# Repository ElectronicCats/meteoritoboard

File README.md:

# Meteorito Board

Kit de estación meteorologica para "Curso de estación y fenómenos meteorológicos" que funciona con La Red Meteorológica Ambiental([RedMet](http://redmet.org/)) promueve la difusión y concientización del cambio climático global. 

Manual, guía de arranque, curso completo y más información en [Pagina Oficial](http://meteorito.mx/index.html)

Electronic Cats invests time and resources providing this open source design, please support Electronic Cats and open-source hardware by purchasing products from Electronic Cats!

Designed by Electronic Cats.

Firmware released under an GNU AGPL v3.0 license. See the LICENSE file for more information.

Hardware released under an CERN Open Hardware Licence v1.2. See the LICENSE_HARDWARE file for more information.

Electronic Cats is a registered trademark, please do not use if you sell these PCBs.

22 July 2017

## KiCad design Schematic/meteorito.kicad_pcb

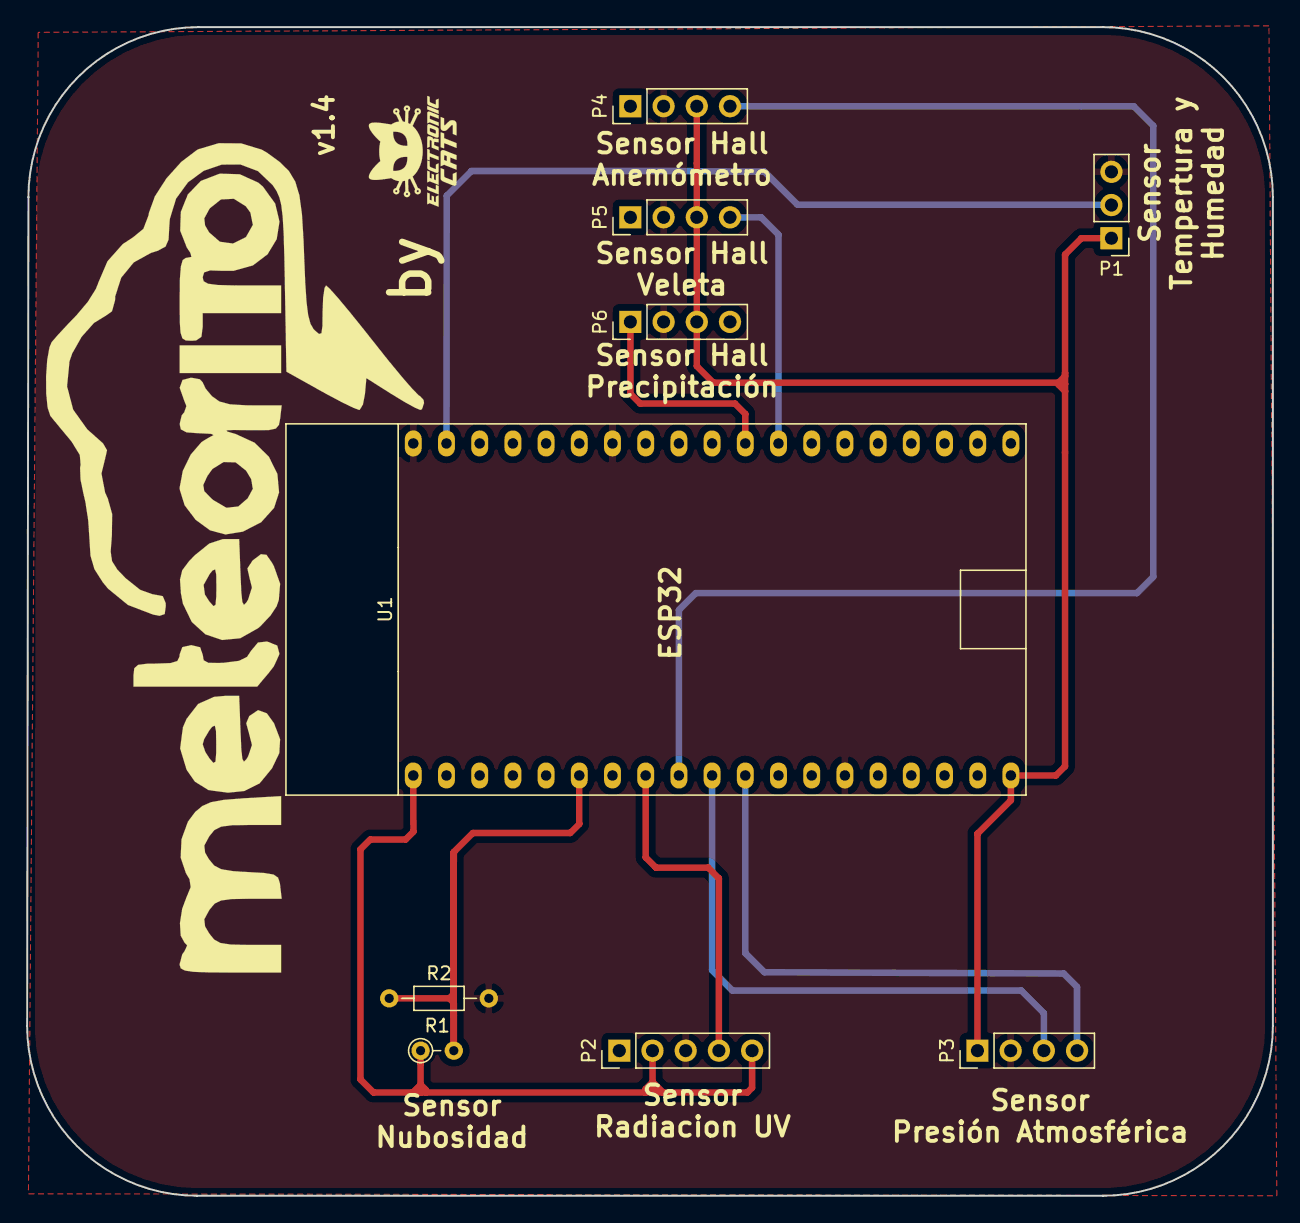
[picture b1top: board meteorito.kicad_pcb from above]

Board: 2 copper layers, 95.3 x 89.4 mm, 10 parts (1 on the bottom side), 11 nets.

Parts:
P1: DH22; PinHeader_1x03_P2.54mm_Vertical
P2: GY-ML8511; PinHeader_1x05_P2.54mm_Vertical
P3: BMP180; PinHeader_1x04_P2.54mm_Vertical
P4: Velocidad; PinHeader_1x04_P2.54mm_Vertical
P5, P6: Precipitacion; PinHeader_1x04_P2.54mm_Vertical
R1: FOTORESISTENCIA; R_Axial_DIN0204_L3.6mm_D1.6mm_P2.54mm_Vertical
R2: 100; R_Axial_DIN0204_L3.6mm_D1.6mm_P7.62mm_Horizontal
U1: ESP32-DEVKIT
svg2mod: electronic; titule_electronic_med

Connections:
+3V3: P2.2, P2.5, R1.1, U1.1
+5V: P1.1, P3.1, P4.3, P5.3, P6.3, U1.19
/AIRE-HALL: P4.4, U1.9
/DHT22: P1.2, U1.37
/IO16: P5.4, U1.27
/IO17: P6.1, U1.28
/IO35: R1.2, R2.1, U1.6
/SCL: P3.3, U1.10
/SDA: P3.4, U1.11
/UV-SENSOR: P2.4, U1.8
GND: P1.3, P2.3, P3.2, P4.2, P5.2, P6.2, R2.2, U1.14, U1.32, U1.38

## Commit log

2017-07-22 added gitignore
2017-07-22 Update gitignore
2017-07-22 Added schematic 0.1
2017-07-22 Images
2017-07-22 Added License hardware
2017-07-22 images board
2017-10-29 Add hardware license
2017-10-29 Añadido ejemplo de conexion a redmet
    Sin test con esp8266
2017-10-30 variable de servidor correcta
2017-10-30 Corregido header Autorizacion
2017-10-30 Corregido formato de envio
2017-10-30 Agregado archivo de configuracion
2017-10-30 Actualizado ino
2017-11-03 Agregado wemos lib
    Añadido etiquetas de conexión
2017-11-10 Agregada funcion de nubosidad
    Sensor Fotoresistencia
2017-11-16 Agregado sensor DHT22
2017-11-16 Agregado temperatura y humedad a variables de ret met
2017-11-16 Corregido error de nubosidad
2017-11-16 Actualizado impresion de variables
2017-11-28 Añadido sensor de UV por I2C VEML6070
2017-11-28 Renombrar variables
2017-11-28 Agregado sensor de presion BMP180
    Presion, Altura y temperatura
2017-11-28 Cambiado mensaje de inicio
2017-11-28 Traduccion de varios textos a español
2017-11-28 Agregado Anemometro
2017-11-28 Configuracion con ESP32
2017-12-01 UV cambiado a entrada analogica
2017-12-01 Agregado direccion del viento
2017-12-01 Agregado precipitacion
2017-12-20 Traducido mas textos de funciones
2017-12-21 Añadida funcion de recepcion de datos
2017-12-21 Cambiados pines de DHT22 y anerometro
    Usado pin 4 en OLED y pin 3 no disponible
2017-12-22 Agregado rango de presion y rayos UV
2018-06-25 Pin DHT22 change
2018-06-25 Cambio de pines y fix nubosidad
2018-07-03 Update conectores
2018-07-03 Actualización de pines
2018-07-17 WiFi o BLE
2018-07-17 Variable para obtener temperatura de DHT22
2018-07-17 Alta de caracteristicas y servicios
2018-07-17 Función para inicializar BLE
2018-07-17 Envio de datos BLE
2018-07-20 Cambio de propiedad de la caracteristica
2018-07-20 end if de la variable que selecciona la comunicación, WiFi o BLE
2018-07-20 end if de la variable que selecciona el método de comunicación
2018-07-20 Variable de control para método de envio
2018-07-20 Cambiando el método de envio de datos en BLE
2018-07-20 Variable de control método de envio
2018-07-20 Direcciones WiFi
2018-07-20 Variable de control
2018-07-20 Remove WiFi direction
2018-07-20 change form char to byte
2018-07-23 Cloudiness Characteristic
2018-07-23 Cloudiness descriptor
2018-07-23 Setting cloudiness characteristic
2018-07-23 Conditional time to connect with WiFi
2018-07-23 Sending cloudiness to te app
2018-07-24 Removing wrong cont
2018-07-24 Create functions EnvioWiFi and BLE
2018-07-24 Actualizacion de informacion
2018-09-14 Se agregaron dos sensores de efecto Hall
2018-09-26 Fix typo
2018-09-26 Update descripcion
2018-09-27 Velocidad del viento trabjando
2018-09-27 Funcion Direccion viento completada
2018-09-27 Precipitación agregado
2018-09-27 Actualización fecha
2018-10-02 Cambios
    Se cambiaron errores que tenían algunos sensores y se asignaron etiquetas a los pines
2018-10-10 FootPrints
    Se asignaron las FootPrints a los pines
2018-10-10 Corregir cambios
2018-10-26 Definicion de PCB
2018-10-30 Medidas iniciales
2018-10-31 Rooteo
2018-10-31 add zones ground
2018-11-01 PCB Terminada
2018-11-13 Corrección
    Se colocaron la tierra y el VCC y se volvio a rootear lo faltante
2018-11-13 Nuevo Rooteo
2018-11-13 Remove NC pins
2018-11-13 Add hole M3
2018-11-14 Screw Hole
2018-11-14 Add image of ESP32
2018-11-14 Add led blink for send data
2018-11-14 Remove ref hole
2018-11-27 Change comment
2018-11-27 update pin UV
2018-11-27 update pin viento
2018-11-27 update precipitacion pin
2019-03-22 revert file
2019-03-22 New ESP32 image
2019-03-22 Add error print
2019-03-27 Changes in ESP32 orientation
2019-03-28 Rerouted
2019-03-28 Sensor Labels added
2019-03-29 remove backups
2019-03-29 v0.2
2019-08-15 inicio pruebas
2019-08-16 remove files
2019-08-16 new define ble descriptor and characteristic
2019-08-16 Interrupt anemometro work
2019-08-16 remove task inncesary
2019-08-16 Fix air velocity
2019-08-19 fix array nubosidad
2019-08-19 update range UV
2019-08-19 change images to wiki
2020-02-13 Review
2020-02-14 Change in track
2020-02-14 fix pines
2020-02-28 Add library update components and layout
2020-03-02 Add labels pins
2020-04-10 Update code
    Update Library SFE_BMP180
    Change code for get pression data
2020-04-14 add app inventor app init
2020-04-16 Update code for app android
2020-04-17 Update App and Firmware
    Add a second service on firmware and update app for android
2020-04-20 Rename path
2020-04-20 Update name contribution
